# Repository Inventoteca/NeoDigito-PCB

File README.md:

# NeoDigito PCB Designs

Seven-segment displays made with Neopixel.  

The Arduino library is here
https://github.com/Inventoteca/NeoDigito

Puedes indicar el número de neopixels por segmento y cambiar colores por cada display.

Recuerda que debes tener instalada la librería de 

Adafruit_NeoPixel

NeoDigito

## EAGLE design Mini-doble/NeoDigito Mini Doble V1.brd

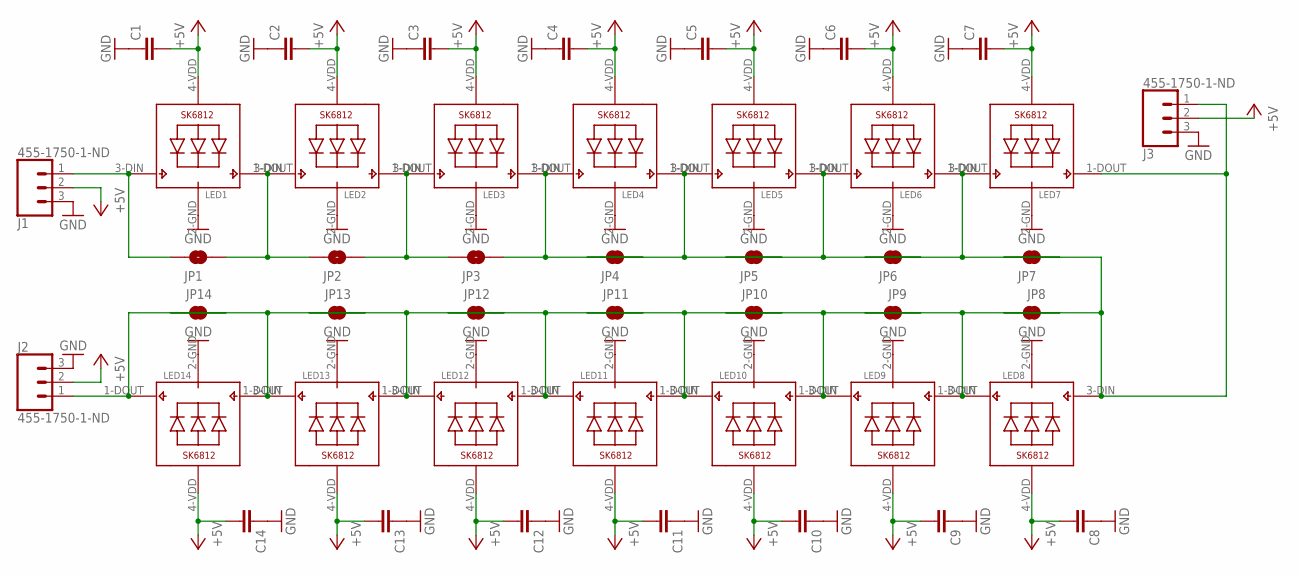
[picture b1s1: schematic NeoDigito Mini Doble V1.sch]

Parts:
C1, C2, C3, C4, C5, C6, C7, C8, C9, C10, C11, C12, C13, C14: C-EUC1206; C1206
J1, J2: 455-1750-1-ND; 1X03
J3: 455-1750-1-ND; 1X03_LONGPADS
JP1, JP2, JP3, JP4, JP5, JP6, JP7, JP8, JP9, JP10, JP11, JP12, JP13, JP14: JUMPER-SMT_2_NO_SILK; SMT-JUMPER_2_NO_SILK
LED1, LED2, LED3, LED4, LED5, LED6, LED7, LED8, LED9, LED10, LED11, LED12, LED13, LED14: SK6812_3535; LED3535

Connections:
+5V: C1.2, C2.2, C3.2, C4.2, C5.2, C6.2, C7.2, C8.2, C9.2, C10.2, C11.2, C12.2, C13.2, C14.2, J1.2, J2.2, J3.2, LED1.4-VDD (VDD), LED2.4-VDD (VDD), LED3.4-VDD (VDD), LED4.4-VDD (VDD), LED5.4-VDD (VDD), LED6.4-VDD (VDD), LED7.4-VDD (VDD), LED8.4-VDD (VDD), LED9.4-VDD (VDD), LED10.4-VDD (VDD), LED11.4-VDD (VDD), LED12.4-VDD (VDD), LED13.4-VDD (VDD), LED14.4-VDD (VDD)
GND: C1.1, C2.1, C3.1, C4.1, C5.1, C6.1, C7.1, C8.1, C9.1, C10.1, C11.1, C12.1, C13.1, C14.1, J1.3, J2.3, J3.3, LED1.2-GND (GND), LED2.2-GND (GND), LED3.2-GND (GND), LED4.2-GND (GND), LED5.2-GND (GND), LED6.2-GND (GND), LED7.2-GND (GND), LED8.2-GND (GND), LED9.2-GND (GND), LED10.2-GND (GND), LED11.2-GND (GND), LED12.2-GND (GND), LED13.2-GND (GND), LED14.2-GND (GND)
unnamed: JP1.2, JP2.1, LED1.1-DOUT (DO), LED2.3-DIN (DI)
unnamed: JP2.2, JP3.1, LED2.1-DOUT (DO), LED3.3-DIN (DI)
unnamed: JP3.2, JP4.2, LED3.1-DOUT (DO), LED4.3-DIN (DI)
unnamed: JP4.1, JP5.2, LED4.1-DOUT (DO), LED5.3-DIN (DI)
unnamed: JP5.1, JP6.2, LED5.1-DOUT (DO), LED6.3-DIN (DI)
unnamed: JP6.1, JP7.2, LED6.1-DOUT (DO), LED7.3-DIN (DI)
unnamed: JP8.1, JP9.2, LED8.1-DOUT (DO), LED9.3-DIN (DI)
unnamed: JP9.1, JP10.2, LED9.1-DOUT (DO), LED10.3-DIN (DI)
unnamed: JP10.1, JP11.2, LED10.1-DOUT (DO), LED11.3-DIN (DI)
unnamed: JP11.1, JP12.2, LED11.1-DOUT (DO), LED12.3-DIN (DI)
unnamed: JP12.1, JP13.2, LED12.1-DOUT (DO), LED13.3-DIN (DI)
unnamed: JP13.1, JP14.2, LED13.1-DOUT (DO), LED14.3-DIN (DI)
unnamed: J3.1, JP7.1, JP8.2, LED7.1-DOUT (DO), LED8.3-DIN (DI)
unnamed: J1.1, JP1.1, LED1.3-DIN (DI)
unnamed: J2.1, JP14.1, LED14.1-DOUT (DO)

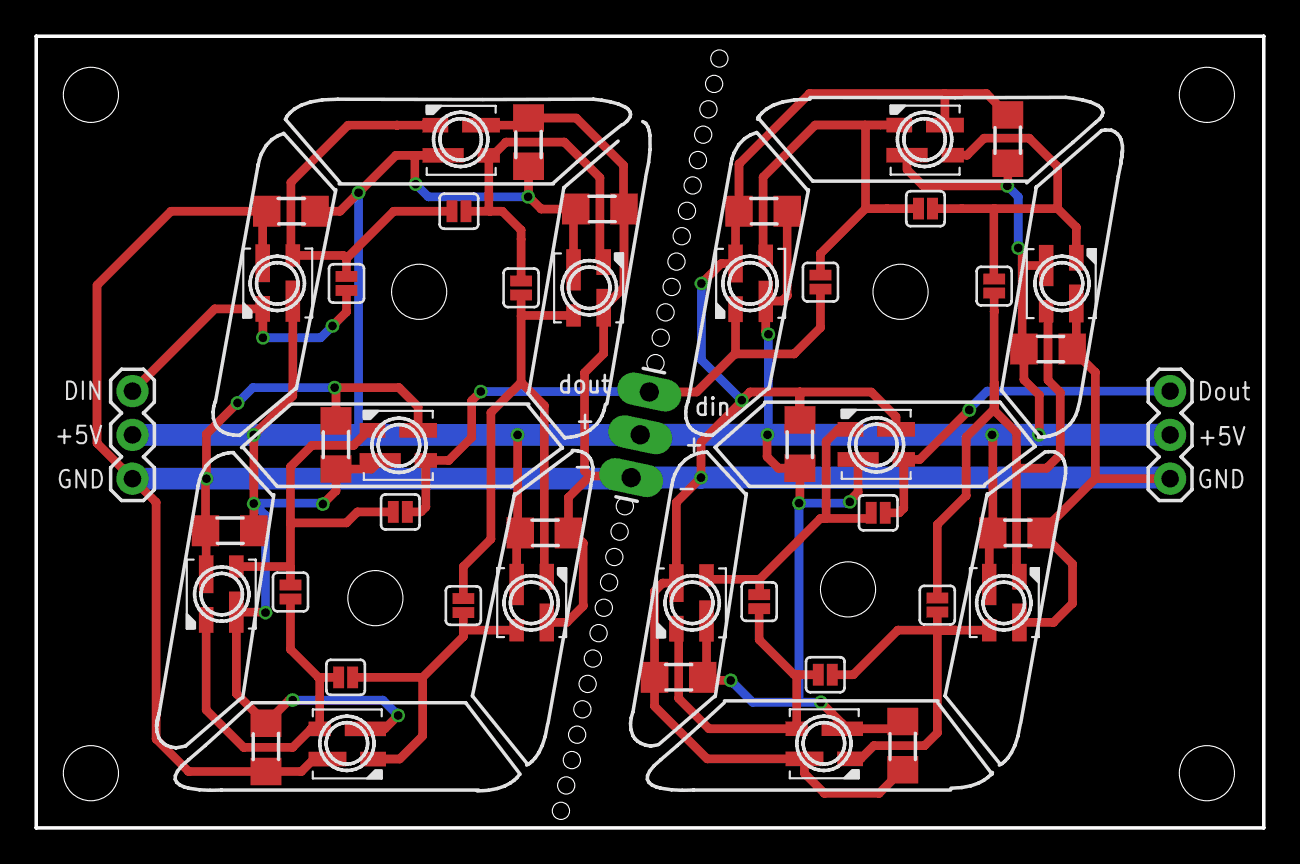
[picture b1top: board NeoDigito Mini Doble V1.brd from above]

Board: 2 copper layers, 71.2 x 45.9 mm, 45 parts (0 on the bottom side), 17 nets.

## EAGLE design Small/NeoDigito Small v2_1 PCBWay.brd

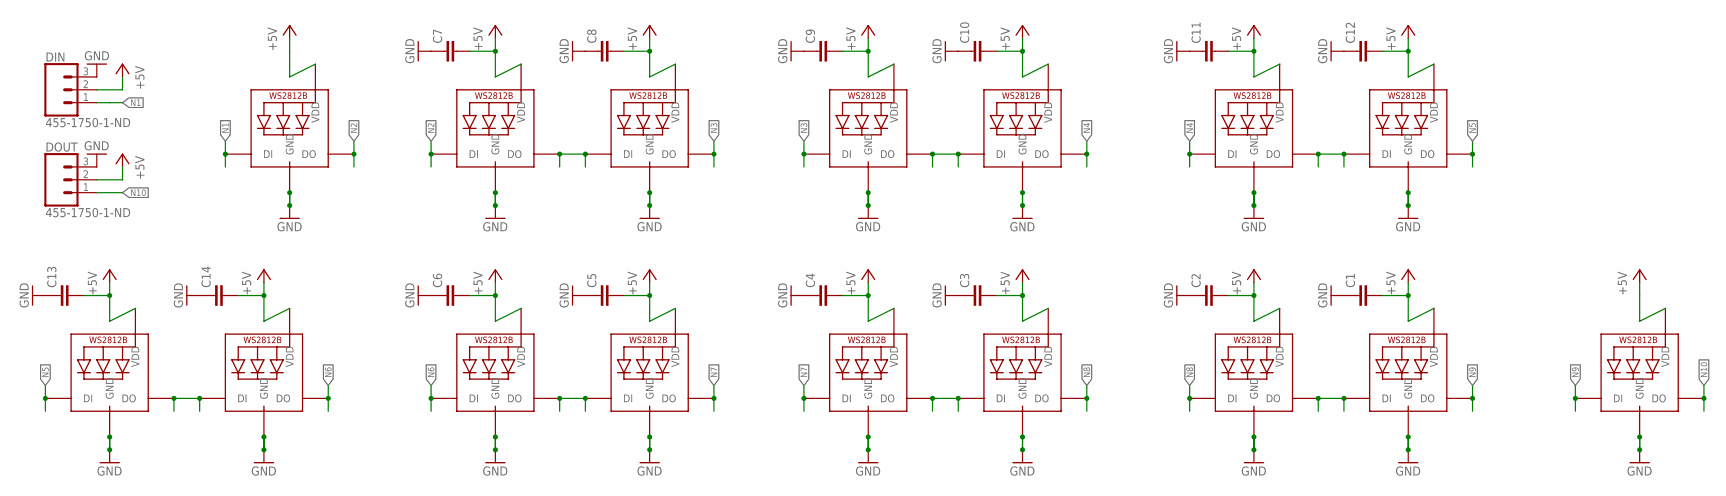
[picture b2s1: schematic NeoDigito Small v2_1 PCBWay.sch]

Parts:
C1, C2, C3, C4, C5, C6, C7, C8, C9, C10, C11, C12, C13, C14: C-EUC0805; C0805
DIN: 455-1750-1-ND; 1X03
DOUT: 455-1750-1-ND; 1X03_NO_SILK
PA.: WS2812B3535; LED3535
PB.: WS2812B3535; LED3535
SA1., SA2.: WS2812B3535; LED3535
SB1., SB2.: WS2812B3535; LED3535
SC1., SC2.: WS2812B3535; LED3535
SD1., SD2.: WS2812B3535; LED3535
SE1., SE2.: WS2812B3535; LED3535
SF1., SF2.: WS2812B3535; LED3535
SG1., SG2.: WS2812B3535; LED3535

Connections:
+5V: C1.2, C2.2, C3.2, C4.2, C5.2, C6.2, C7.2, C8.2, C9.2, C10.2, C11.2, C12.2, C13.2, C14.2, DIN.2, DOUT.2, PA..2 (VDD), PB..2 (VDD), SA1..2 (VDD), SA2..2 (VDD), SB1..2 (VDD), SB2..2 (VDD), SC1..2 (VDD), SC2..2 (VDD), SD1..2 (VDD), SD2..2 (VDD), SE1..2 (VDD), SE2..2 (VDD), SF1..2 (VDD), SF2..2 (VDD), SG1..2 (VDD), SG2..2 (VDD)
GND: C1.1, C2.1, C3.1, C4.1, C5.1, C6.1, C7.1, C8.1, C9.1, C10.1, C11.1, C12.1, C13.1, C14.1, DIN.3, DOUT.3, PA..4 (GND), PB..4 (GND), SA1..4 (GND), SA2..4 (GND), SB1..4 (GND), SB2..4 (GND), SC1..4 (GND), SC2..4 (GND), SD1..4 (GND), SD2..4 (GND), SE1..4 (GND), SE2..4 (GND), SF1..4 (GND), SF2..4 (GND), SG1..4 (GND), SG2..4 (GND)
N1: DIN.1, PB..1 (DI)
N2: PB..3 (DO), SC1..1 (DI)
N3: SC2..3 (DO), SD1..1 (DI)
N4: SD2..3 (DO), SE1..1 (DI)
N5: SE2..3 (DO), SG1..1 (DI)
N6: SB1..1 (DI), SG2..3 (DO)
N7: SA1..1 (DI), SB2..3 (DO)
N8: SA2..3 (DO), SF1..1 (DI)
N9: PA..1 (DI), SF2..3 (DO)
N10: DOUT.1, PA..3 (DO)
unnamed: SE1..3 (DO), SE2..1 (DI)
unnamed: SC1..3 (DO), SC2..1 (DI)
unnamed: SA1..3 (DO), SA2..1 (DI)
unnamed: SF1..3 (DO), SF2..1 (DI)
unnamed: SD1..3 (DO), SD2..1 (DI)
unnamed: SG1..3 (DO), SG2..1 (DI)
unnamed: SB1..3 (DO), SB2..1 (DI)

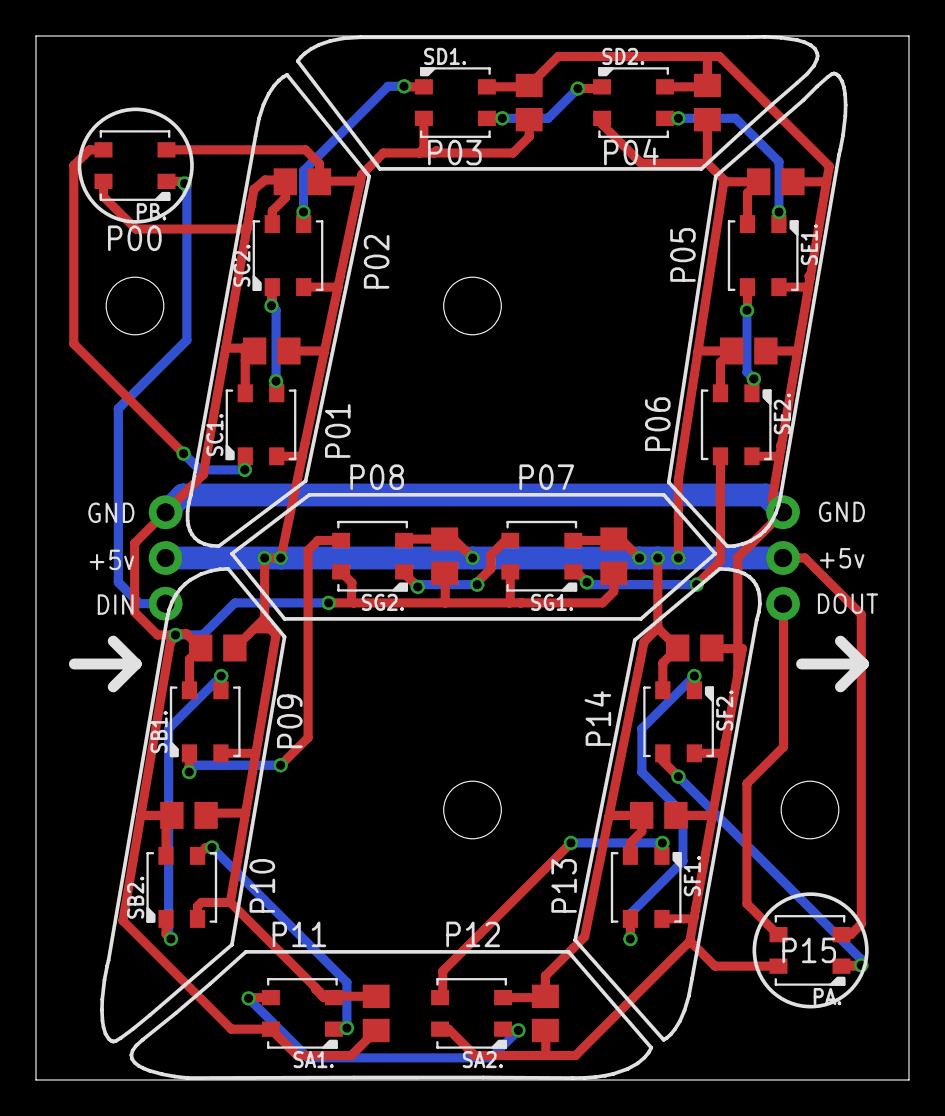
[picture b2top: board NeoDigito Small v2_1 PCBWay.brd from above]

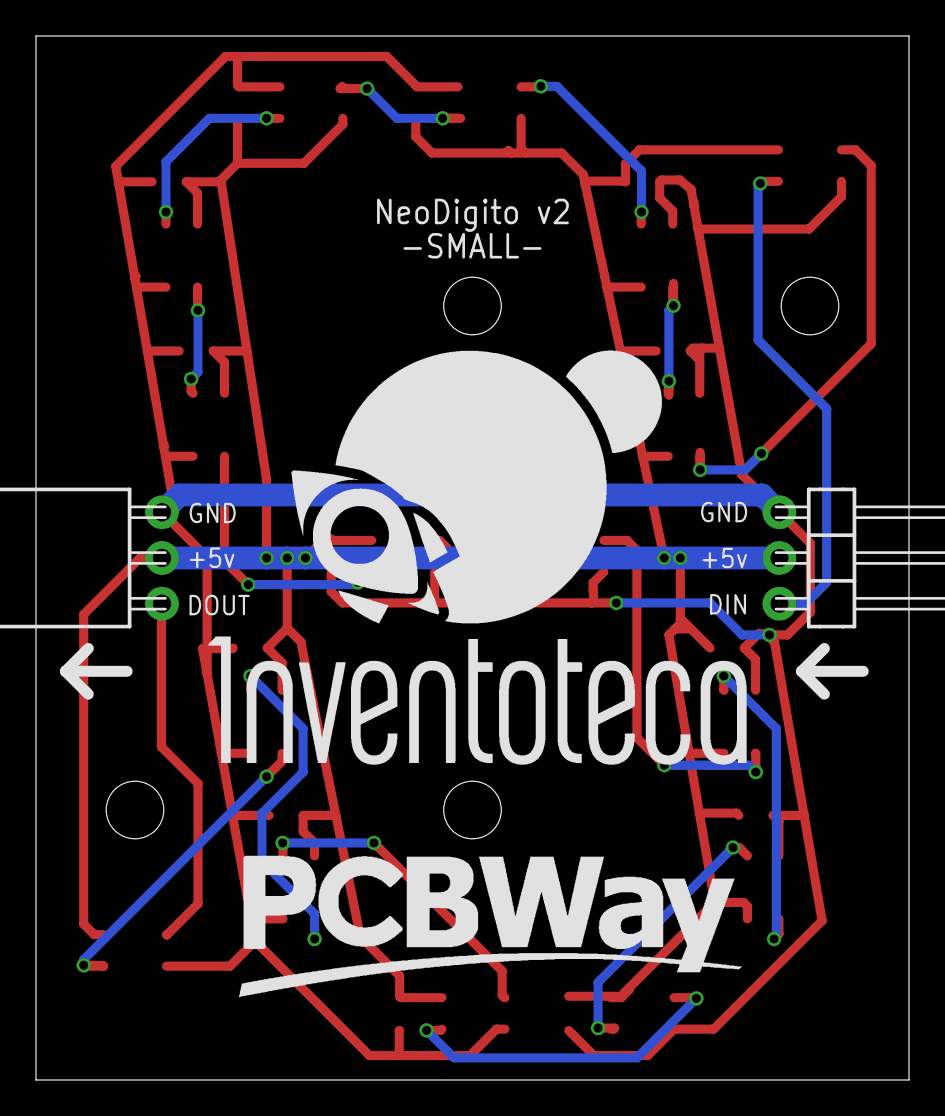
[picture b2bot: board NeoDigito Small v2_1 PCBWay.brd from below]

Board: 2 copper layers, 48.5 x 58.0 mm, 32 parts (2 on the bottom side), 19 nets.

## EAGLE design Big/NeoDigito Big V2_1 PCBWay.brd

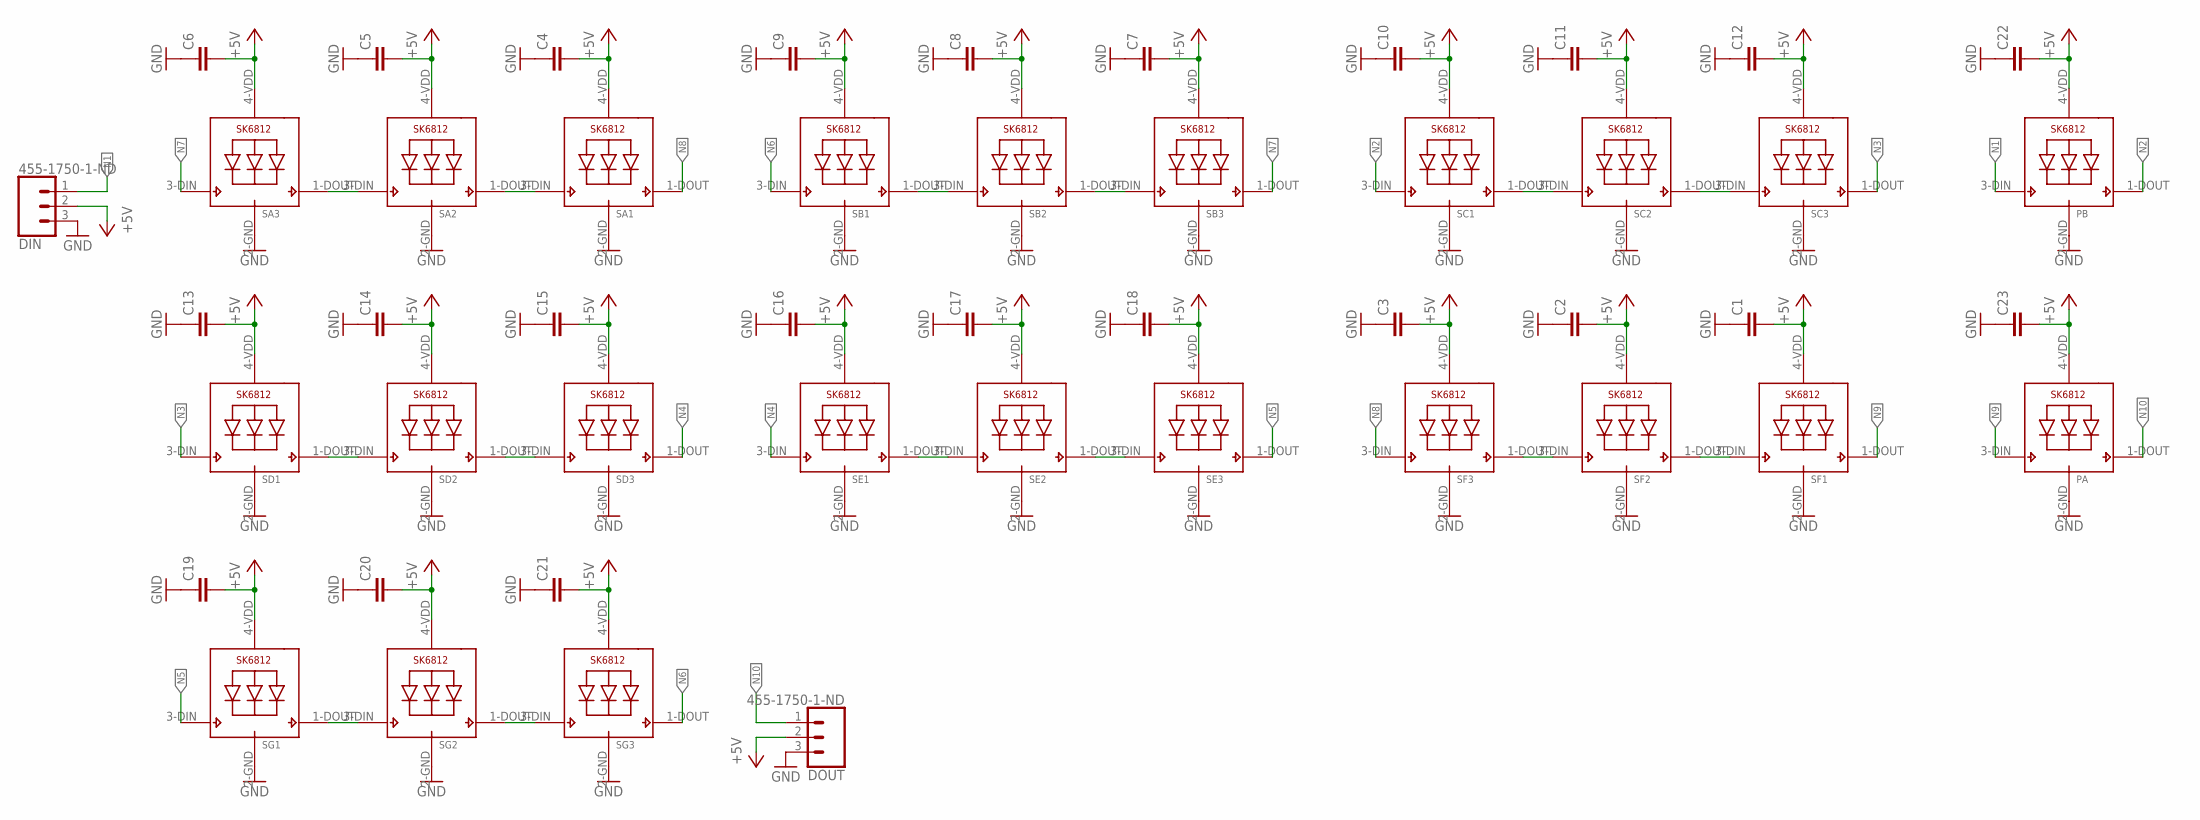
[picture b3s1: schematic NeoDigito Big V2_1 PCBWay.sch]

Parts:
C1, C2, C3, C4, C5, C6, C7, C8, C9, C10, C11, C12, C13, C14, C15, C16, C17, C18, C19, C20, C21, C22, C23: C-EUC0805; C0805
DIN: 455-1750-1-ND; 1X03
DOUT: 455-1750-1-ND; 1X03_NO_SILK
PA: SK6812_3535; LED3535
PB: SK6812_3535; LED3535
SA1, SA2, SA3: SK6812_3535; LED3535
SB1, SB2, SB3: SK6812_3535; LED3535
SC1, SC2, SC3: SK6812_3535; LED3535
SD1, SD2, SD3: SK6812_3535; LED3535
SE1, SE2, SE3: SK6812_3535; LED3535
SF1, SF2, SF3: SK6812_3535; LED3535
SG1, SG2, SG3: SK6812_3535; LED3535

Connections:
+5V: C1.2, C2.2, C3.2, C4.2, C5.2, C6.2, C7.2, C8.2, C9.2, C10.2, C11.2, C12.2, C13.2, C14.2, C15.2, C16.2, C17.2, C18.2, C19.2, C20.2, C21.2, C22.2, C23.2, DIN.2, DOUT.2, PA.4-VDD (VDD), PB.4-VDD (VDD), SA1.4-VDD (VDD), SA2.4-VDD (VDD), SA3.4-VDD (VDD), SB1.4-VDD (VDD), SB2.4-VDD (VDD), SB3.4-VDD (VDD), SC1.4-VDD (VDD), SC2.4-VDD (VDD), SC3.4-VDD (VDD), SD1.4-VDD (VDD), SD2.4-VDD (VDD), SD3.4-VDD (VDD), SE1.4-VDD (VDD), SE2.4-VDD (VDD), SE3.4-VDD (VDD), SF1.4-VDD (VDD), SF2.4-VDD (VDD), SF3.4-VDD (VDD), SG1.4-VDD (VDD), SG2.4-VDD (VDD), SG3.4-VDD (VDD)
GND: C1.1, C2.1, C3.1, C4.1, C5.1, C6.1, C7.1, C8.1, C9.1, C10.1, C11.1, C12.1, C13.1, C14.1, C15.1, C16.1, C17.1, C18.1, C19.1, C20.1, C21.1, C22.1, C23.1, DIN.3, DOUT.3, PA.2-GND (GND), PB.2-GND (GND), SA1.2-GND (GND), SA2.2-GND (GND), SA3.2-GND (GND), SB1.2-GND (GND), SB2.2-GND (GND), SB3.2-GND (GND), SC1.2-GND (GND), SC2.2-GND (GND), SC3.2-GND (GND), SD1.2-GND (GND), SD2.2-GND (GND), SD3.2-GND (GND), SE1.2-GND (GND), SE2.2-GND (GND), SE3.2-GND (GND), SF1.2-GND (GND), SF2.2-GND (GND), SF3.2-GND (GND), SG1.2-GND (GND), SG2.2-GND (GND), SG3.2-GND (GND)
N1: DIN.1, PB.3-DIN (DI)
N2: PB.1-DOUT (DO), SC1.3-DIN (DI)
N3: SC3.1-DOUT (DO), SD1.3-DIN (DI)
N4: SD3.1-DOUT (DO), SE1.3-DIN (DI)
N5: SE3.1-DOUT (DO), SG1.3-DIN (DI)
N6: SB1.3-DIN (DI), SG3.1-DOUT (DO)
N7: SA3.3-DIN (DI), SB3.1-DOUT (DO)
N8: SA1.1-DOUT (DO), SF3.3-DIN (DI)
N9: PA.3-DIN (DI), SF1.1-DOUT (DO)
N10: DOUT.1, PA.1-DOUT (DO)
unnamed: SA2.3-DIN (DI), SA3.1-DOUT (DO)
unnamed: SA1.3-DIN (DI), SA2.1-DOUT (DO)
unnamed: SB1.1-DOUT (DO), SB2.3-DIN (DI)
unnamed: SB2.1-DOUT (DO), SB3.3-DIN (DI)
unnamed: SC1.1-DOUT (DO), SC2.3-DIN (DI)
unnamed: SC2.1-DOUT (DO), SC3.3-DIN (DI)
unnamed: SD1.1-DOUT (DO), SD2.3-DIN (DI)
unnamed: SD2.1-DOUT (DO), SD3.3-DIN (DI)
unnamed: SG1.1-DOUT (DO), SG2.3-DIN (DI)
unnamed: SG2.1-DOUT (DO), SG3.3-DIN (DI)
unnamed: SE1.1-DOUT (DO), SE2.3-DIN (DI)
unnamed: SE2.1-DOUT (DO), SE3.3-DIN (DI)
unnamed: SF2.3-DIN (DI), SF3.1-DOUT (DO)
unnamed: SF1.3-DIN (DI), SF2.1-DOUT (DO)

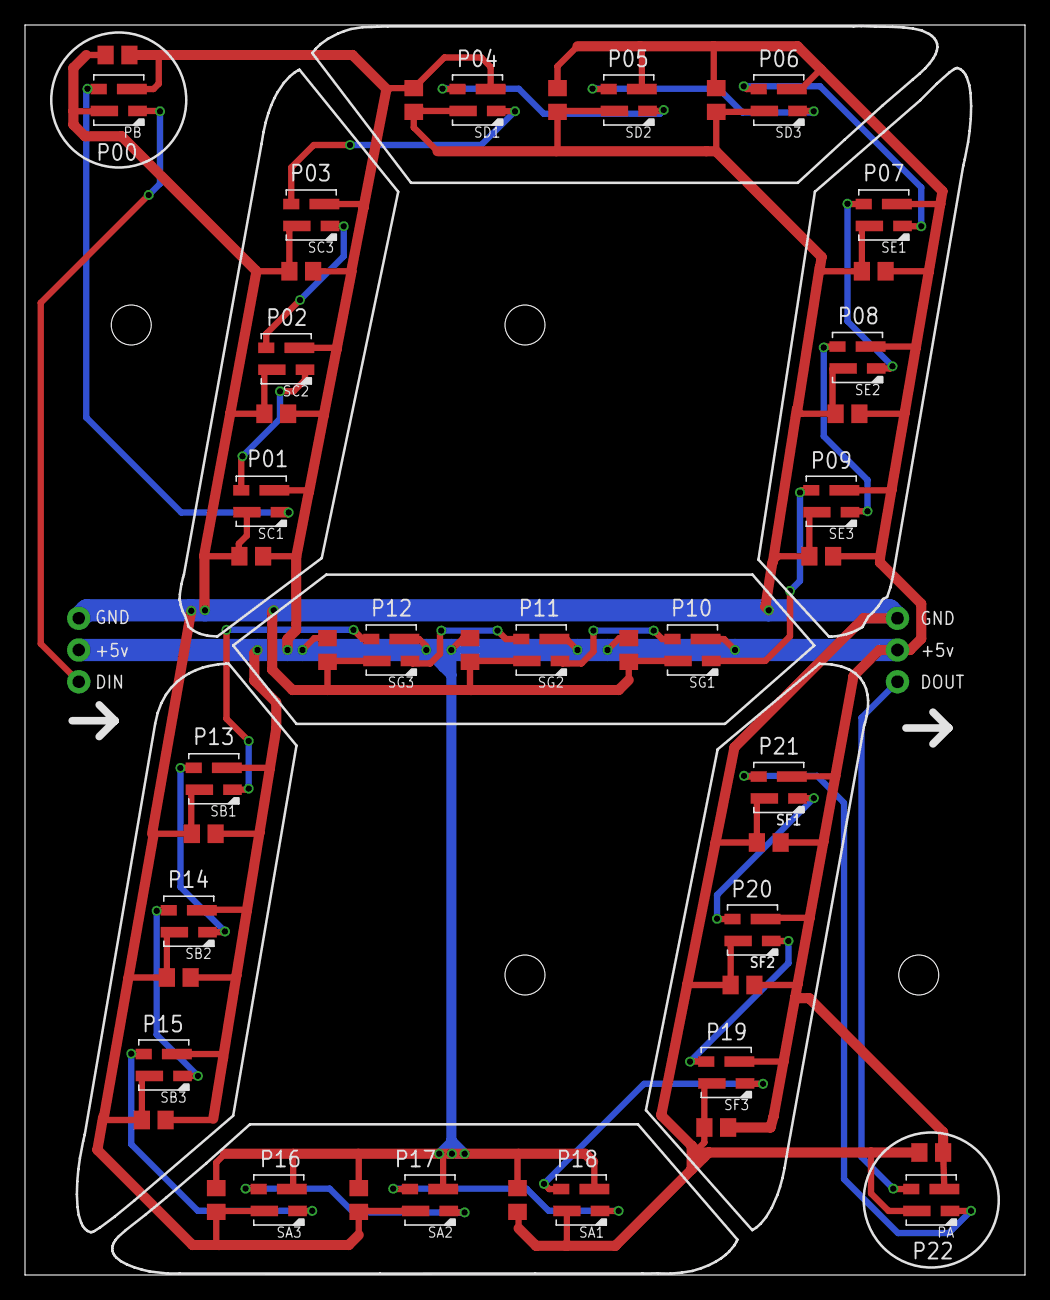
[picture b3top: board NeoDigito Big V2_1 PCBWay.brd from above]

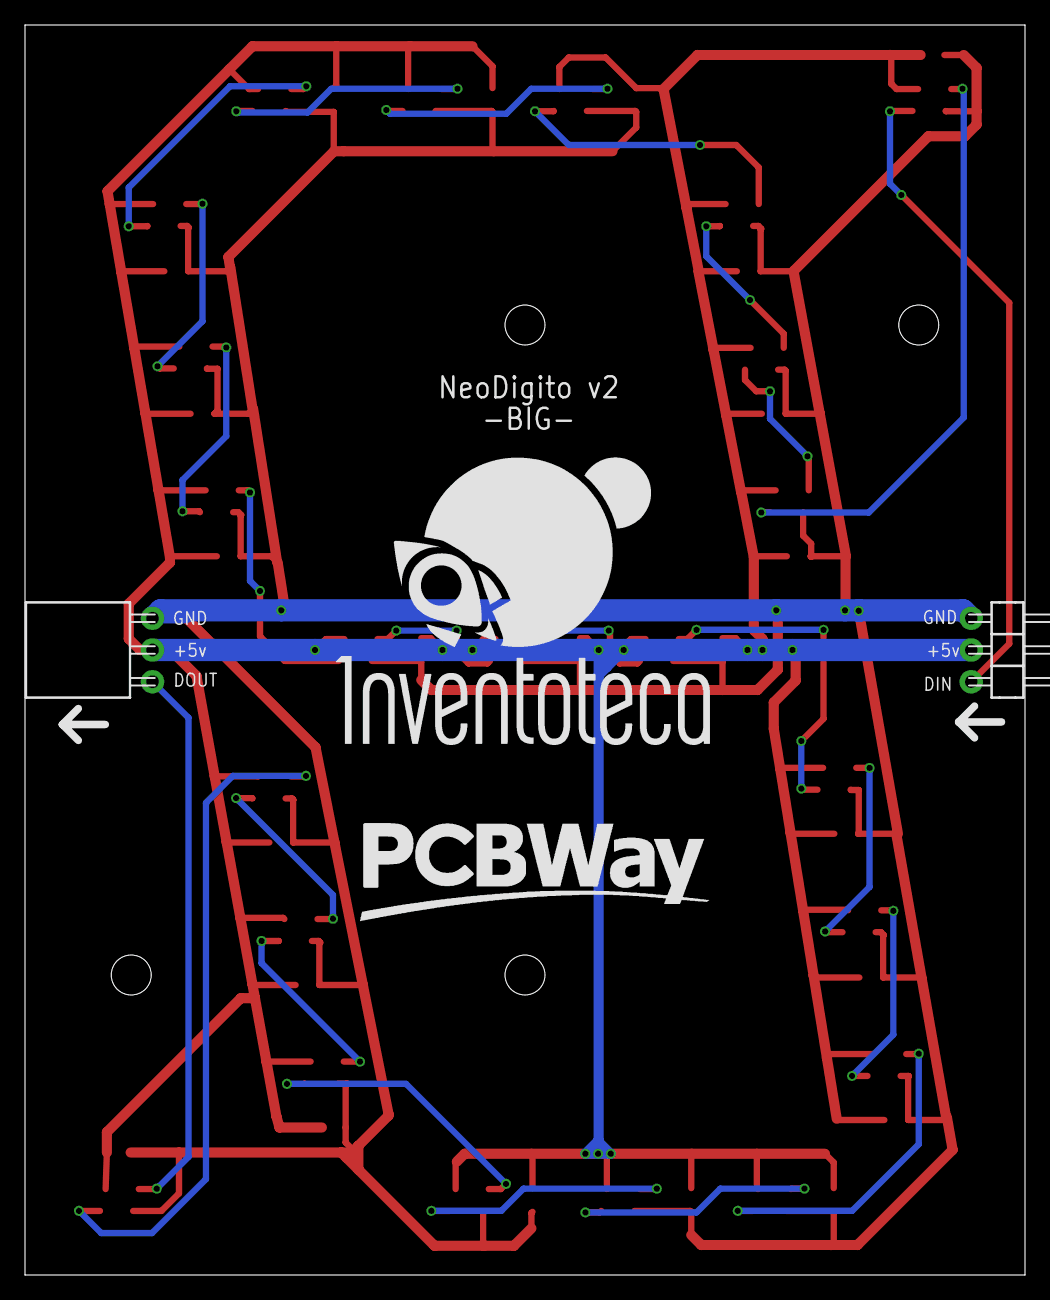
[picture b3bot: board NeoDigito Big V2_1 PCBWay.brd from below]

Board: 2 copper layers, 80.0 x 100.0 mm, 48 parts (2 on the bottom side), 26 nets.

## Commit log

2021-12-07 Primer respaldo
    Se migraron los archivos del repositorio de NeoDigito a Neodigito-PCB
2022-04-01 Rotate boards (big and small) and rename files
2022-04-01 small update
2023-01-11 poner logo
2023-01-11 ignore Eagle backup files
2023-01-11 new mini single digit
2023-01-11 with pcbway logo

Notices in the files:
parts and their libraries:
SparkFun-Jumpers: Licensing: Creative Commons ShareAlike 4.0 International - https://creativecommons.org/licenses/by-sa/4.0
